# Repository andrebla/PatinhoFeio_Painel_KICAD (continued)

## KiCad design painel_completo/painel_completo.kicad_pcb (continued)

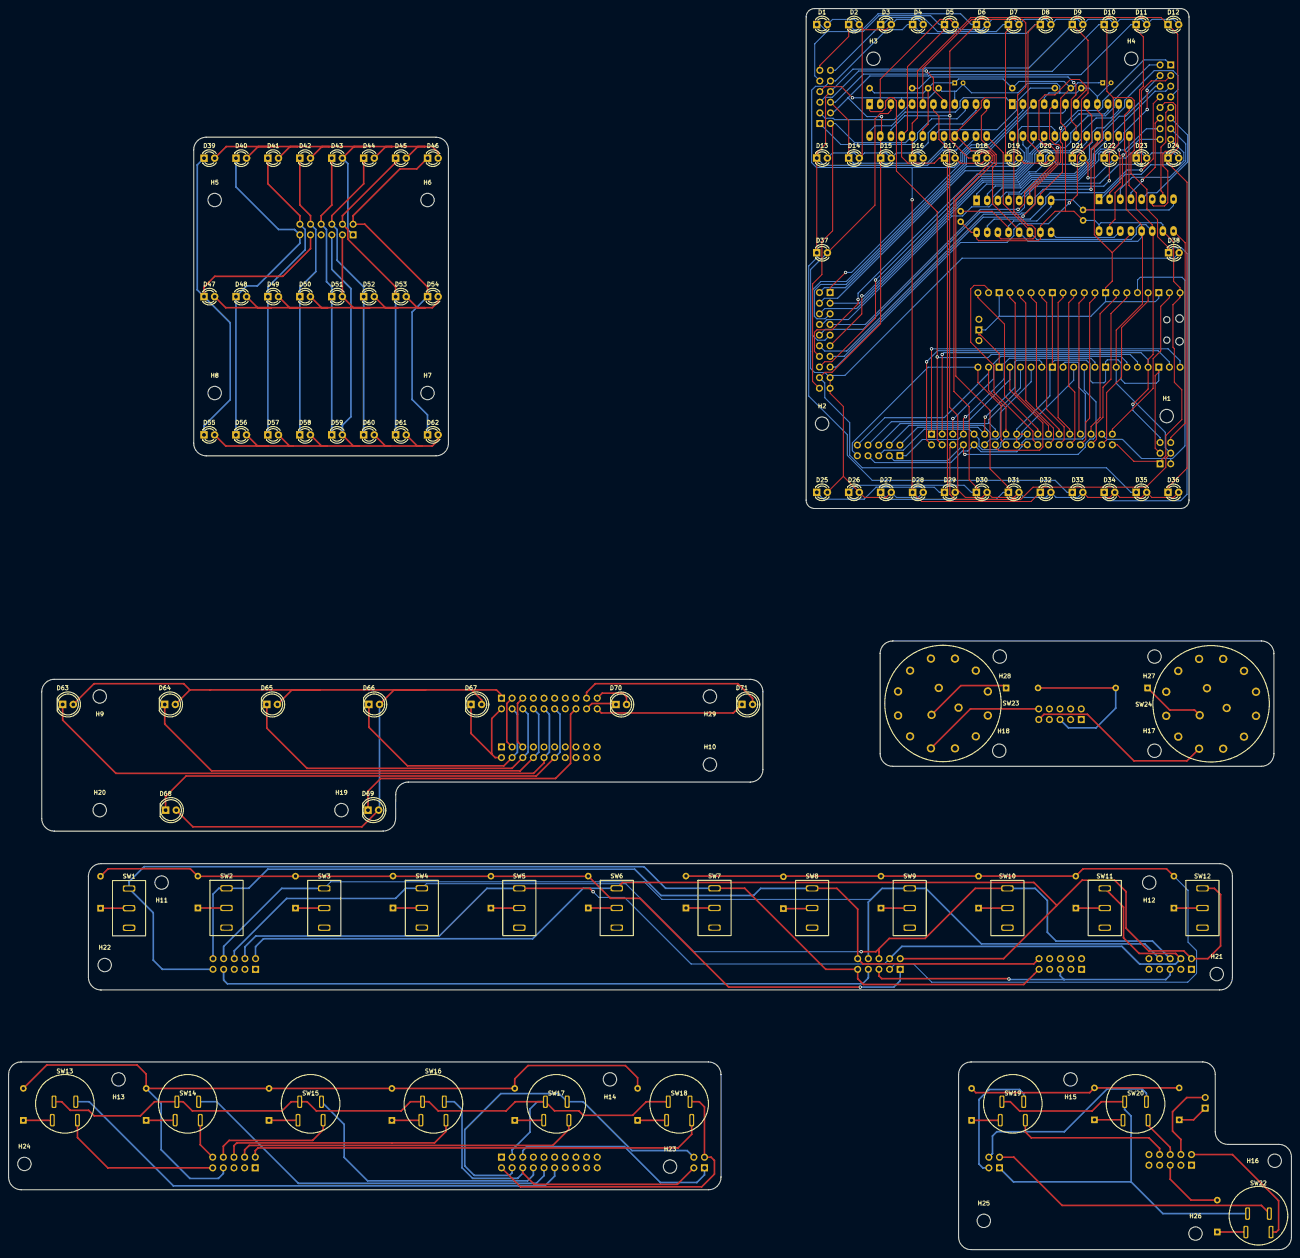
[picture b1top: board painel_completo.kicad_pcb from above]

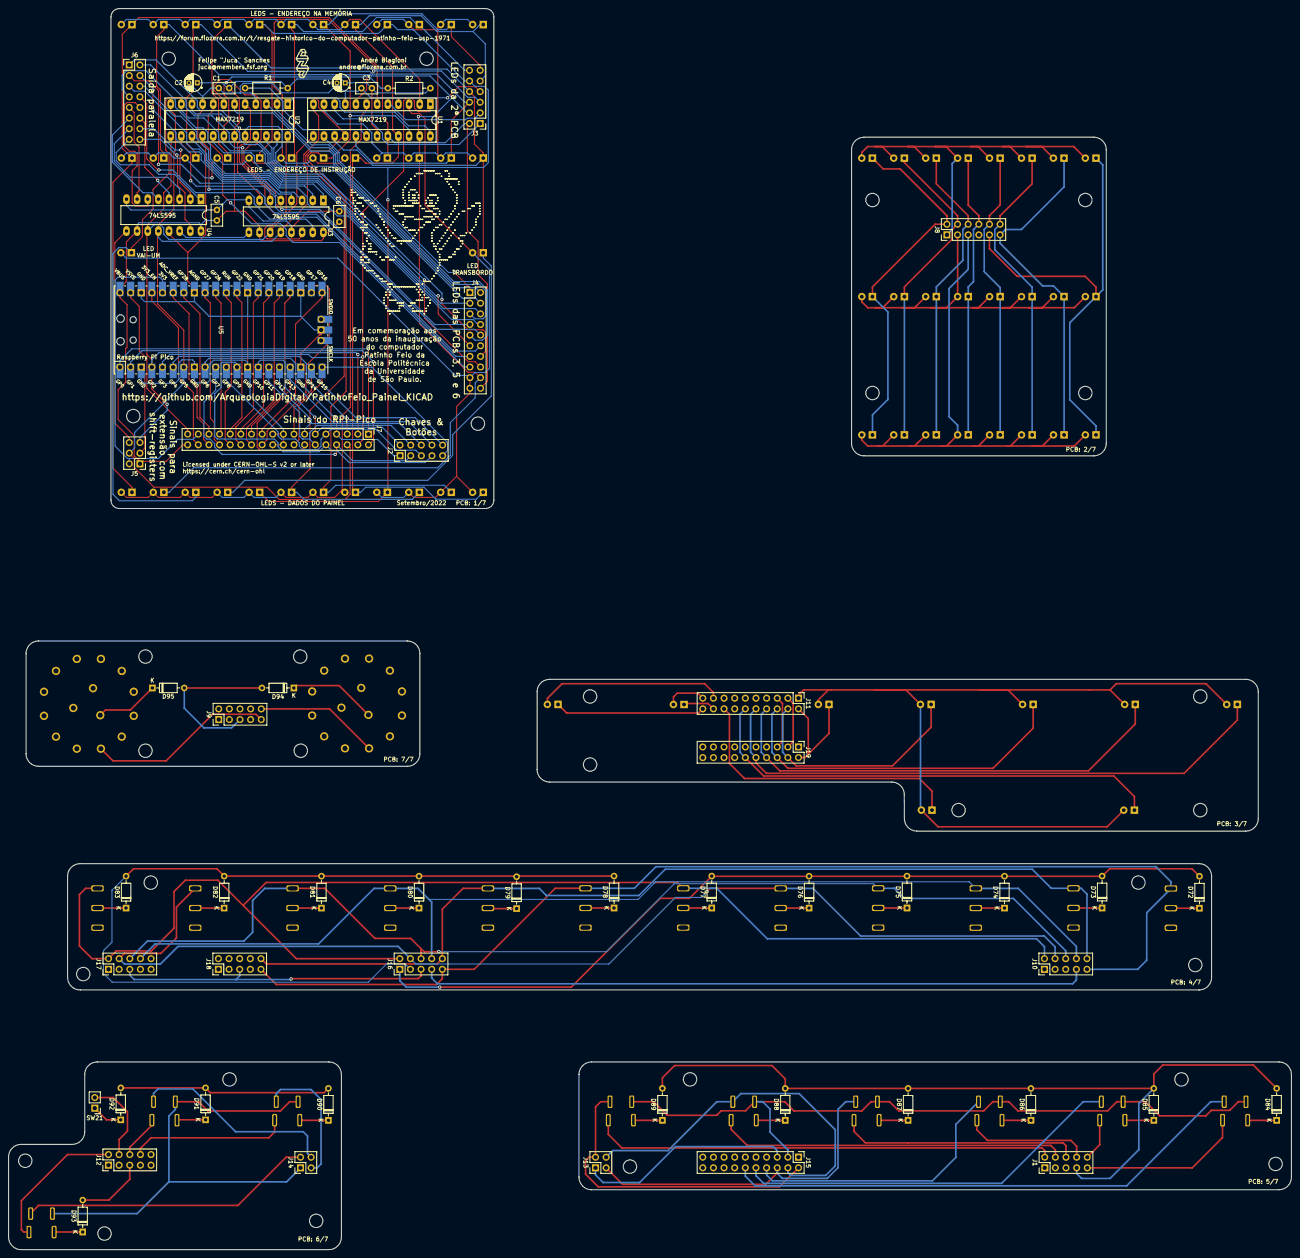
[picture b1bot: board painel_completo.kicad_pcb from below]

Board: 2 copper layers, 306.3 x 296.4 mm, 180 parts (57 on the bottom side), 122 nets.

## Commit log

2022-09-13 adição painel completo
2022-09-13 adição furos fixação e alteração máscara de componentes
2022-09-13 alteração máscara de componentes da pcb1
